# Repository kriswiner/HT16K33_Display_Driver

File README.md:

HT16K33_Display_Driver
======================

Simple demo of driving 4, four-digit, seven-segment [HP QDSP-6064 bubble displays](https://www.sparkfun.com/products/12710) with one [HT16K33 display driver](http://www.adafruit.com/datasheets/ht16K33v110.pdf)

Each HT16K33 cathode pin can drive two display cathodes. The HT16K33 has eight cathode pins and 16 anode pins. Therefore, the RAM Mapping HT16K33 can drive a total of 128 LED segments. So a total of four, 4-digit, 7-segment displays can be driven with this one chip with just 2 TWI wires and power and ground. That is a lot of display without taking up a lot of the GPIO pins.

I decided to try to reduce this idea of driving four bubble displays to practice; what follows is what I did and how it worked out.

First I breadboarded the circuit with Adafruit's [HT16K33 breakout board] (http://www.adafruit.com/products/1427) shown here:

Here is what my initial circuit looked like. The HT16K33 is powered by the 3.3 V reference from and connected to the I2C of an 8 MHz Pro Mini Arduino microcontroller.

I was able to easily get two bubble displays running from the HT16K33 breakout on my little breadboard. I actually added a third display using jumper wires to another breadboard just to prove that I really could drive four (well, at least three!) of the bubble displays at a time with just one HT16K33.

After that success, I spent most of a Saturday soldering up a circuit on a perf board with four bubble displays and one HT16K33. This is what it looks like:

Look at all those wires! This is not a great picture but you can see that all four displays are working using the display driver sketch in this repository, which currently displays floating point (top left and bottom right) or integer (top right and bottom left) numbers of four digits or less. The sketch has simple utility but is good enough to display temperature, time, and other sensor output.

The last step was biting the bullet and learning how to use Eagle CAD to design a PCB with the same circuit. It took only a few days mostly because: 1) I was able to take advantage of all the work Adafruit and [uChip](https://github.com/uChip/BubbleDisplay) had already done and, 2) I got a lot of help from Jim Lindblom of [Sparkfun] (http://www.sparkfun.com) and Dan Sheadel of [OSHPark] (http://www.oshpark.com), where I am having the first prototypes made. Here is what the boards will look like at almost actual size! (1.48 x 1.58 inches).

..........

I received the boards from OSHPark and promptly put the components on. A bad picture of the board is shown above. It was straightforward to solder even the small diode; 0805 passive components are easy to handle with a good pair of tweezers. Using a soldering iron for surface mounted components is doable but the solder joints are never going to look like machine-made parts do without a lot of practice. I noticed that the displays worked just fine mounted in their through holes before soldering; I guess there is enough contact to allow the proper current flow even without soldering. I assembled all three boards and---they all worked! I love it when this happens. This is what the boards look like in action.

The board is connected to an Arduino 3.3 V 8 MHz Pro Mini running the sketch in this repository. Notice that there are only four wires, not the rat's nest of wires from the perf board prototype. So what are the advantages of this "FrontPack" design over conventional LED display choices?  Well, 1) you don't need external current-limiting resistors with the HT16K33 chip, 2) you can run the display board wih 3.3 V or 5 V as you wish, 3) it only takes four wires to control up to 8 x 4 four-digit displays since up to eight of these "FrontPacks" can be independently addressed in a given circuit by soldering a unique 3-bit address on the board pads, 4) it has a rather small footprint at 1.48 x 1.58 inches square so it saves space, and 5) it is so retro cool!

This is the first prototype; there are several variants I can think of that might be more useful for a given application. For example, why not mount the HT16K33 on the back to make a conventional "BackPack" version of this display. This would come in handy for mounting on a cased surface. The FrontPack (I'll toss the scare quotes from now on) has the additional attribute that the bubble displays, even fully inserted into the through holes, stand proud of the top surface of the HT16K33 chip, meaning that even the FrontPack can be mounted, albeit a little more awkwardly, on an inner case surface with only the displays visible outside. But the really neat thing about the bubble displays and this through-hole mounting is that the displays can be soldered into the board at a tilt angle to aid viewing and can stand as much as a millimeter prouder still of the HT16K33 chip by a judicious choice of how far to push the displays into the board before soldering. Bottom line: even the FrontPack is likely to suit most needs.

Now there is a quirk with the current setup (there always is!). I noticed a curious unwanted behavior with this driver chip. The sketch works as intended when I have the displays numbered in (the somewhat unintuitive) order 1-2-3-4 from top right to bottom left. When I change the order to go from top left to bottom right (the more intuitive ordering), everything still works but the minus sign on displays 1 and 3 becomes intermittent. I don’t understand this behavior yet, but I suspect it has something to do with the RAM ordering of the multiplexing coupled with the particular way I am constructing the characters to display.  That is, I am hoping it is a subtle software error and not some hidden limitation of the chip. It doesn’t get in the way of using any or all of the displays, but in the interest of full disclosure, I thought I would mention this oddity. If anyone spots my error in the sketch above I would appreciate a heads up.

This is version v.01 and there are a few things I would do differently. I noticed that Adafruit (from whom I shamelessly copied the idea of using the HT16K33) used a 24 mil trace for their VDD and GND lines. This is good practice that I would follow next time but didn't here. Likewise, putting the capacitor right next to ground is OK, but it might be better to place it right next to the VDD pin on the HT16K33, instead. I used 4.7 kOhm resistors as pull-ups for the SDA and SCL lines since I am currently in the habit of using fast (400 kHz) I2C. This is in contrast to the 10 kOhm pullups used by Adafruit. I'd stick with the 4.7 kOhm in the next design iteration. Lastly, I used 39 kOhm resistors in the address lines as specified in the HT16K33 data sheet instead of the 47 kOhm resistors used by Adafruit. They probably just had a lot of these 47 kOhm resistors lying around.

I had a lot of fun designing this board, my first real experience with Eagle CAD, and I must close by thanking Adafruit for showiing me how to use this wonderful chip by Holtek, uChip from whom I shamelessly borrowed the QDSP-6064 Eagle device package and who has devised a different solution to using these retro cool bubble displays, and Sparkfun Electronics for their cheery answers to all my inane questions, and somehow providing an inexpensive supply of these quirky, odd looking, lovable bubble displays.

Despite standing on the shoulders of these giants, I take full responsibility for any and all errors in the sketch or Eagle design. I would only ask that you tell me when you find an error so I can do my best to fix it.

Update: Well I think I figured out the display ordering problem. In some sense I organized the displays backward. I think the HT16K33 prefers to roll through the RAM map sequentially and if I try to display out of order the chip has a harder time with the multiplexing. This is probably a direct result of my copying Adafruit's and uChip's schematics which were arranged for "backpack" displays, not the "frontpack" design I am using. I can still get any display or all the displays to function correctly, but it's somewhat annoying to have the top right display be number one  and then go top right to top left, then bottom right to bottom left instead of the more intuitive top left to top right, bottom left to bottom right ordering. The proper way to use this chip is to display to C0-3 A0-7, then C4-7 A0-7, then C0-3 A8-15, and finally C4-7 A8-15, I think. In any case, I took the opportunity to "fix" the design by swapping the top left bubble display with the top right one, etc., in a version 2 of the design. I also reduced the size of the board by 6% by avoiding setting traces outside, on the far side, of the bubble displays. Adafruit used 24 mil traces for their power and ground, so that's what I am using in the new design. I was using 10 mil traces everywhere else in version 1 and I maintained that in version 2. Finally, I shrunk the vias down to 15 mil diameter so I won't have gigantic holes all over the board. I ordered three boards from OSH Park and when they arrive and I assemble and test the new version, I will report the results. Here is what the new boards will look like:

....

I got the boards assembled and tested and they look pretty good! They are a little smaller than the first version, don't have that annoying display order problem, and have a slightly more rational trace pattern as well as thicker traces for power and ground. Here are a few photos:

The display is showing data from the BMP-180 pressure sensor. Top left is temperature in degrees Fahrenheit, top right is pressure in kiloPascals, bottom right is elevation in feet and bottom left in meters. This is a very convenient way to display numerical data. It's not as much information as can be displayed on a 16 x 2 LCD or 48 x 84 Nokia 5110 LCD display, both of which I use and love, but it only requires four wires compared to the seven or eight for the other displays. And of course, the bubble display is way retro cooler, too!

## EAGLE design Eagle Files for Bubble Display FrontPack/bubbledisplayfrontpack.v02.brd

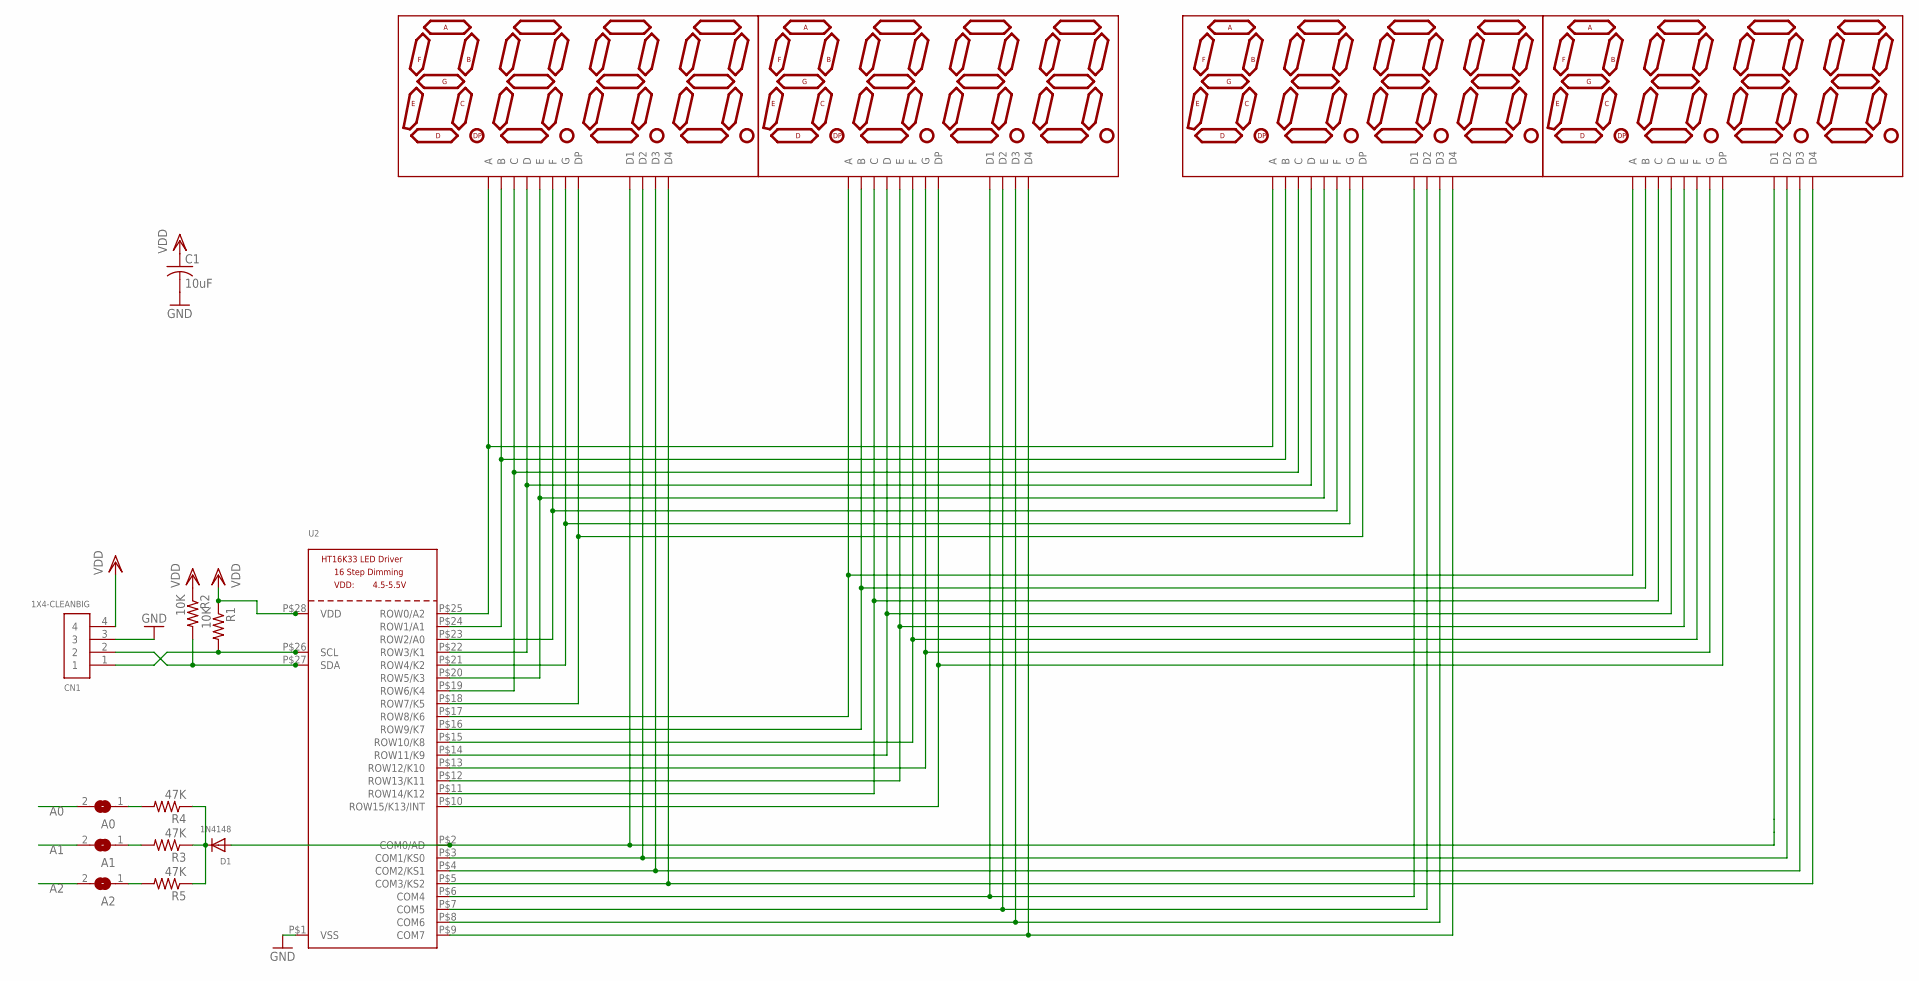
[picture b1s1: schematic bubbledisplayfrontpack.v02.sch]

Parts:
A0, A1, A2: SOLDERJUMPERREFLOW_NOPASTE; SOLDERJUMPER_REFLOW_NOPASTE
C1: 10uF; C0805K
CN1: 1X4-CLEANBIG; 1X04-CLEANBIG
D1: 1N4148; SOD-323F
DISPLAY1, DISPLAY2, DISPLAY3, DISPLAY4: hp; DIL12
R1, R2: 10K; R0805
R3, R4, R5: 47K; R0805
U2: HT16K33_SOP28; SOP28_300MIL

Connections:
A0: A0.2, DISPLAY1.9 (F), DISPLAY3.9 (F), U2.P$23 (ROW2/A0)
A1: A1.2, DISPLAY1.11 (B), DISPLAY3.11 (B), U2.P$24 (ROW1/A1)
A2: A2.2, DISPLAY1.12 (A), DISPLAY3.12 (A), U2.P$25 (ROW0/A2)
C0P1: D1.A, DISPLAY2.1 (D1), DISPLAY3.1 (D1), U2.P$2 (COM0/AD)
C1P10: DISPLAY2.10 (D2), DISPLAY3.10 (D2), U2.P$3 (COM1/KS0)
C2P4: DISPLAY2.4 (D3), DISPLAY3.4 (D3), U2.P$4 (COM2/KS1)
C3P6: DISPLAY2.6 (D4), DISPLAY3.6 (D4), U2.P$5 (COM3/KS2)
C4P1: DISPLAY1.1 (D1), DISPLAY4.1 (D1), U2.P$6 (COM4)
C5P10: DISPLAY1.10 (D2), DISPLAY4.10 (D2), U2.P$7 (COM5)
C6P4: DISPLAY1.4 (D3), DISPLAY4.4 (D3), U2.P$8 (COM6)
C7P6: DISPLAY1.6 (D4), DISPLAY4.6 (D4), U2.P$9 (COM7)
GND: C1.2, CN1.3, U2.P$1 (VSS)
unnamed: D1.C, R3.1, R4.1, R5.1
unnamed: DISPLAY1.8 (D), DISPLAY3.8 (D), U2.P$22 (ROW3/K1)
unnamed: DISPLAY2.9 (F), DISPLAY4.9 (F), U2.P$15 (ROW10/K8)
unnamed: A2.1, R5.2
unnamed: DISPLAY2.2 (E), DISPLAY4.2 (E), U2.P$12 (ROW13/K11)
unnamed: A1.1, R3.2
unnamed: A0.1, R4.2
SCL: CN1.1, R1.2, U2.P$26 (SCL)
SDA: CN1.2, R2.2, U2.P$27 (SDA)
SEGAD24P12: DISPLAY2.12 (A), DISPLAY4.12 (A), U2.P$17 (ROW8/K6)
SEGBD24P11: DISPLAY2.11 (B), DISPLAY4.11 (B), U2.P$16 (ROW9/K7)
SEGCP3: DISPLAY2.3 (C), DISPLAY4.3 (C), U2.P$11 (ROW14/K12)
SEGD13EP2: DISPLAY1.7 (G), DISPLAY3.7 (G), U2.P$21 (ROW4/K2)
SEGD13GP7: DISPLAY1.3 (C), DISPLAY3.3 (C), U2.P$19 (ROW6/K4)
SEGDD24P8: DISPLAY2.8 (D), DISPLAY4.8 (D), U2.P$14 (ROW11/K9)
SEGDPD13P5: DISPLAY1.5 (DP), DISPLAY3.5 (DP), U2.P$18 (ROW7/K5)
SEGDPP5: DISPLAY2.5 (DP), DISPLAY4.5 (DP), U2.P$10 (ROW15/K13/INT)
SEGED13P2: DISPLAY1.2 (E), DISPLAY3.2 (E), U2.P$20 (ROW5/K3)
SEGFP9: DISPLAY2.7 (G), DISPLAY4.7 (G), U2.P$13 (ROW12/K10)
VDD: C1.1, CN1.4, R1.1, R2.1, U2.P$28 (VDD)

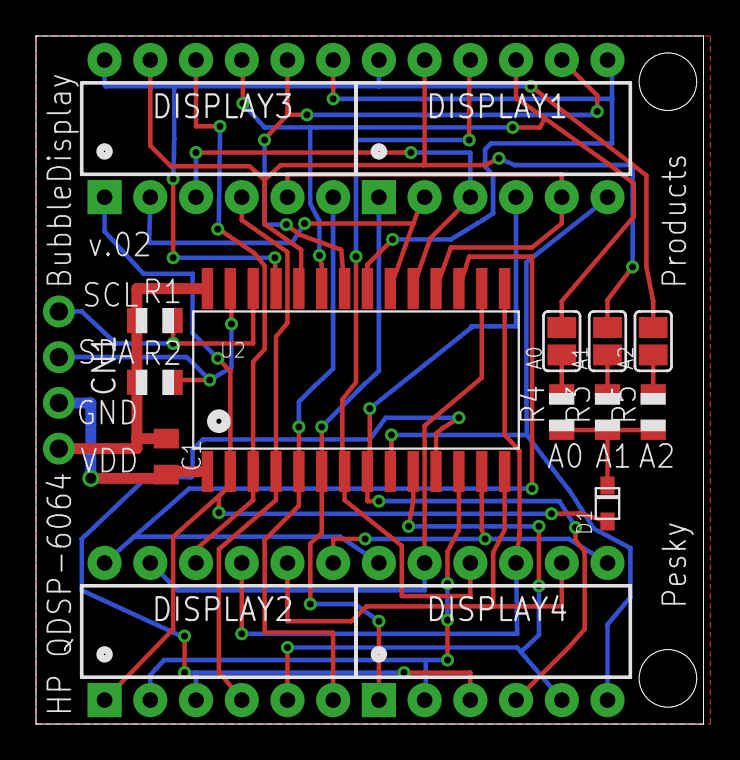
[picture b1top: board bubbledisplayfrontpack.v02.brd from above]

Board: 2 copper layers, 37.1 x 38.2 mm, 16 parts (0 on the bottom side), 32 nets.

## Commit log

2014-05-09 Create HT16K33DisplayDriver
    Demonstrate basic functionality including parameterizing the register addresses, initializing the display,
    writing integers to one of four seven segment LED displays.
2014-05-09 Update HT16K33DisplayDriver
2014-06-02 Updated four four displays run on one HT16K33
2014-06-02 Rename HT16K33DisplayDriver to HT16K33DisplayDriver.ino
2014-06-22 Add Eagle files for BubbleDisplayFrontPack v.01
    First prototype of using the HT16K33 RAM Mapping 16*8 LED Driver to
    display to 4 four-digit, eight-segment QDSP-6064 bubble displays.
2014-06-22 BubbleDisplayFrontPackDesign.v01
    HT16K33 RAM Mapping 16*8 LED Driver with 4 four-digit, eight-segment
    QDSP-6064 bubble displays in a "frontpack" board design
2014-06-25 Added BubbleDisplayFrontpack.v02 Eagle files

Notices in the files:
parts and their libraries:
SparkFun-Displays: Licensing: Creative Commons ShareAlike 4.0 International - https://creativecommons.org/licenses/by-sa/4.0
